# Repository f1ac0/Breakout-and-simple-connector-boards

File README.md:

# Breakout and simple connector boards
This repository contains mostly simple KiCAD PCBs boards that I needed at some point.

# Disclaimer
This is a hobbyist project, it comes with no warranty and no support.

I publish my work under the CC-BY-NC-SA license.

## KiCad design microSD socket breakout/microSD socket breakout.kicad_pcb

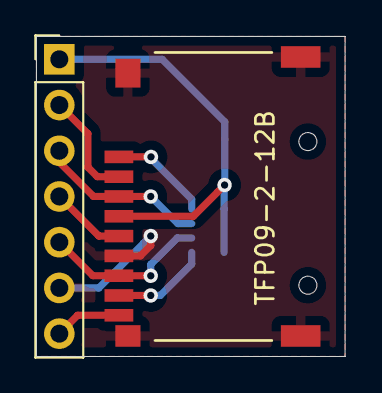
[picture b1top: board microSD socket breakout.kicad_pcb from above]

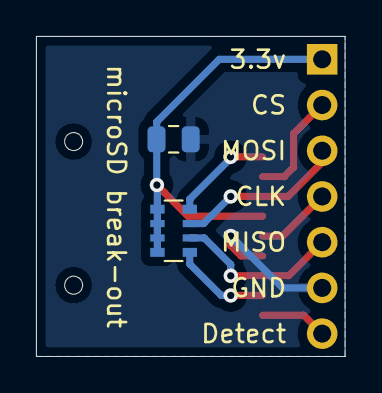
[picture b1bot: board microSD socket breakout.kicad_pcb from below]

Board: 2 copper layers, 17.1 x 17.8 mm, 4 parts (2 on the bottom side), 9 nets.

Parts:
C1: C_Small; C_0805_2012Metric
J1: Micro_SD_Card_Det_1Pin; TFP09-2-12B
J2: Conn_01x07; PinHeader_1x07_P2.54mm_Vertical
RN1: R_Pack04; R_Array_Convex_4x0603

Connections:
+3.3V: C1.1, J1.4 (VDD), J2.1, RN1.5 (R4.2), RN1.6 (R3.2), RN1.7 (R2.2), RN1.8 (R1.2)
/SD_DETECT: J1.9 (CARD_DETECTION), J2.7
/SPI_CLK: J1.5 (CLK), J2.4
/SPI_CS: J1.2 (DAT3/CD), J2.2
/SPI_MISO: J1.7 (DAT0), J2.5, RN1.2 (R2.1)
/SPI_MOSI: J1.3 (CMD), J2.3, RN1.3 (R3.1)
GND: C1.2, J1.6 (VSS), J1.10 (SHIELD), J2.6
unnamed: J1.1 (DAT2), RN1.4 (R4.1)
unnamed: J1.8 (DAT1), RN1.1 (R1.1)

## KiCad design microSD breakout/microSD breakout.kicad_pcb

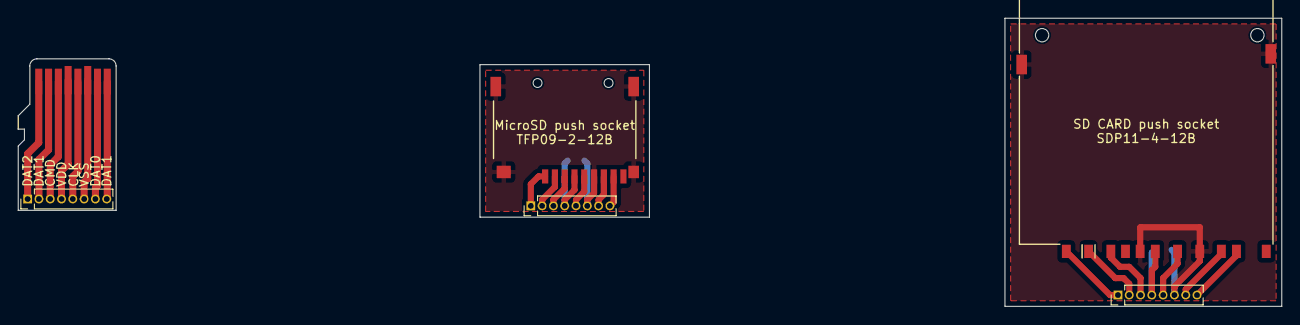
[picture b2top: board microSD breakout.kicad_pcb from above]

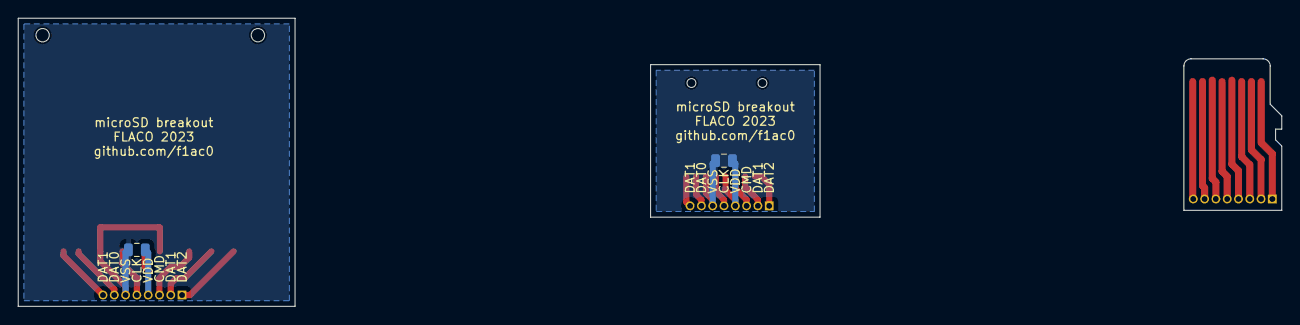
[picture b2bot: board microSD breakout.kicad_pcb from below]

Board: 2 copper layers, 142.0 x 32.4 mm, 8 parts (2 on the bottom side), 24 nets.

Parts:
C1, C2: C_Small; C_0805_2012Metric
J1, J4, J6: Conn_01x08; PinHeader_1x08_P1.27mm_Vertical
J2: Micro_SD_Card_Det_1Pin; TFP09-2-12B
J3: Micro_SD_Card; Micro_SD
J5: SD_Card; Conn_SDcard

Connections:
/SD_CLK: J3.5 (CLK), J4.5
/SD_CMD: J3.3 (CMD), J4.3
/SD_DAT0: J3.7 (DAT0), J4.7
/SD_DAT1: J3.8 (DAT1), J4.8
/SD_DAT2: J3.1 (DAT2), J4.1
/SD_DAT3: J3.2 (DAT3/CD), J4.2
/SD_VDD: J3.4 (VDD), J4.4
/SD_VSS: J3.6 (VSS), J4.6
/SOCKSD_CLK: J5.5 (CLK), J6.5
/SOCKSD_CMD: J5.2 (CMD), J6.3
/SOCKSD_DAT0: J5.7 (DAT0), J6.7
/SOCKSD_DAT1: J5.8 (DAT1), J6.8
/SOCKSD_DAT2: J5.9 (DAT2), J6.1
/SOCKSD_DAT3: J5.1 (CD/DAT3), J6.2
/SOCKSD_VDD: C2.1, J5.4 (VDD), J6.4
/SOCKSD_VSS: C2.2, J5.3 (VSS), J5.6 (VSS), J5.12 (SHELL1), J5.13 (SHELL2), J6.6
/SOCK_CLK: J1.5, J2.5 (CLK)
/SOCK_CMD: J1.3, J2.3 (CMD)
/SOCK_DAT0: J1.7, J2.7 (DAT0)
/SOCK_DAT1: J1.8, J2.8 (DAT1)
/SOCK_DAT2: J1.1, J2.1 (DAT2)
/SOCK_DAT3: J1.2, J2.2 (DAT3/CD)
/SOCK_VDD: C1.1, J1.4, J2.4 (VDD)
/SOCK_VSS: C1.2, J1.6, J2.6 (VSS), J2.10 (SHIELD)

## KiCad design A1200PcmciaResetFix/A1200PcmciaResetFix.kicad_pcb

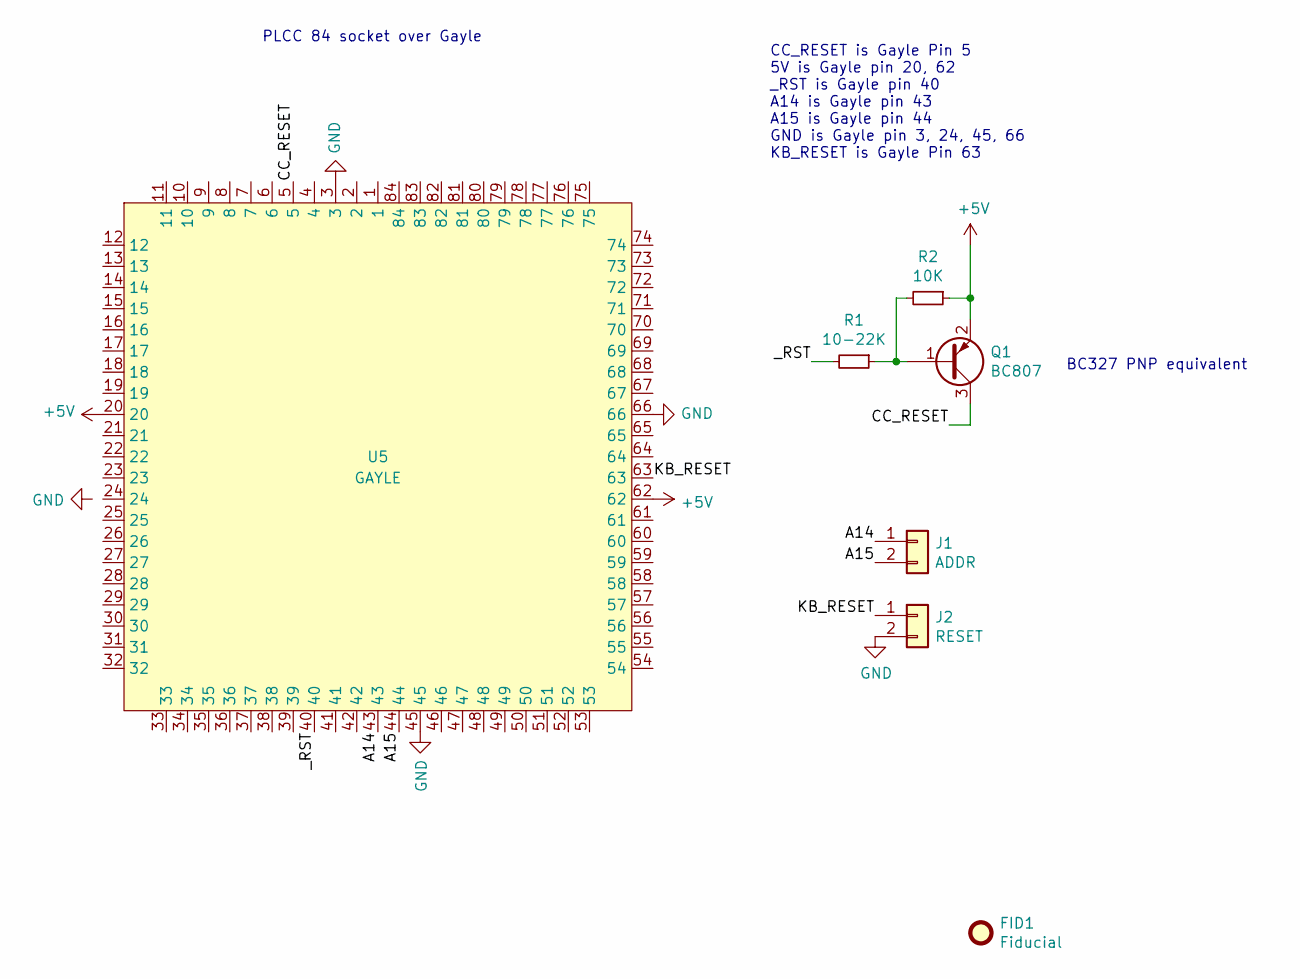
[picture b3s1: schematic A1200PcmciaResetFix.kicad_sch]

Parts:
FID1: Fiducial; CC_BY_NC_SA_square_silkscreen
J1: ADDR; PinHeader_1x02_P2.54mm_Vertical
J2: RESET; PinHeader_1x02_P2.54mm_Vertical
Q1: BC807; SOT-23
R1: 10-22K; R_0805_2012Metric
R2: 10K; R_0805_2012Metric
U5: GAYLE; PLCC-84_THT-SocketOnTop

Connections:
+5V: Q1.2 (E), R2.1, U5.20, U5.62
/A14: J1.1, U5.43
/A15: J1.2, U5.44
/CC_RESET: Q1.3 (C), U5.5
/KB_RESET: J2.1, U5.63
/_RST: R1.2, U5.40
GND: J2.2, U5.3, U5.45, U5.66
unnamed: Q1.1 (B), R1.1, R2.2

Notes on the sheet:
CC_RESET is Gayle Pin 5 5V is Gayle pin 20, 62 _RST is Gayle pin 40 A14 is Gayle pin 43 A15 is Gayle pin 44 GND is Gayle pin 3, 24, 45, 66 KB_RESET is Gayle Pin 63
BC327 PNP equivalent
PLCC 84 socket over Gayle

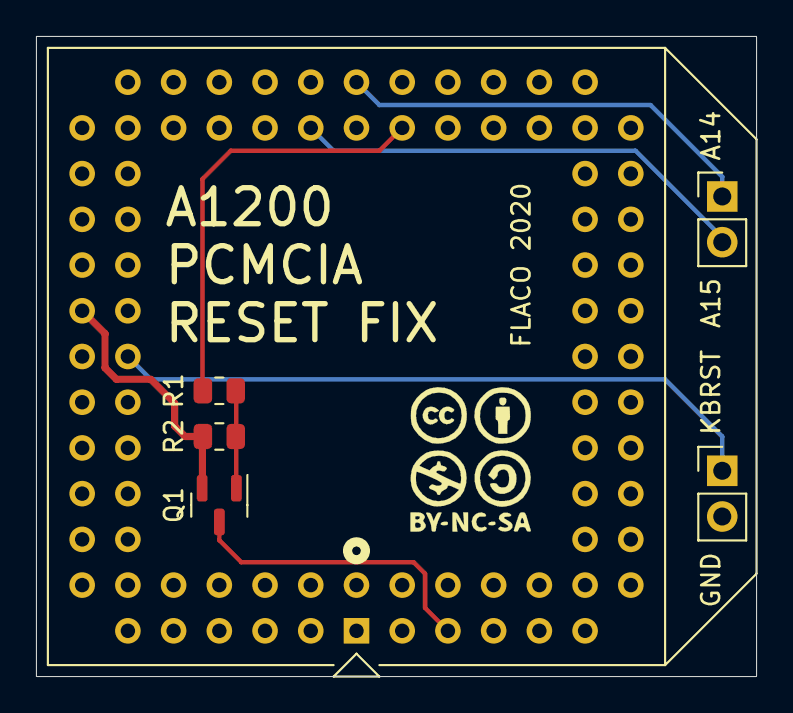
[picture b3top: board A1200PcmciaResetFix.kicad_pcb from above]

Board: 2 copper layers, 40.0 x 35.6 mm, 7 parts (1 on the bottom side), 8 nets.

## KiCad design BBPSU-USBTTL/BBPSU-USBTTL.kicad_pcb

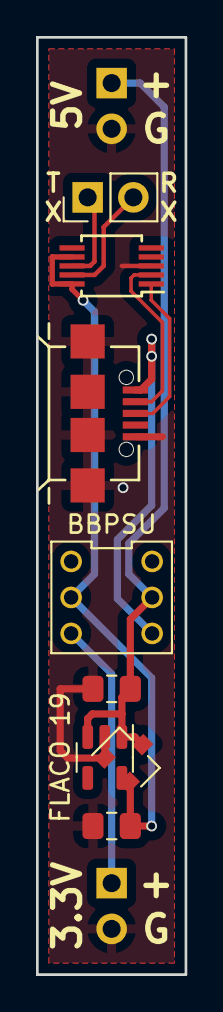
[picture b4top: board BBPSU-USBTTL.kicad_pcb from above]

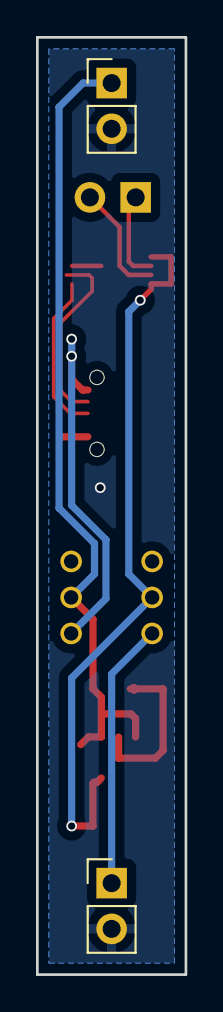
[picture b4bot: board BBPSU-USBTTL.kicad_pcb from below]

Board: 2 copper layers, 8.3 x 52.1 mm, 10 parts (2 on the bottom side), 9 nets.

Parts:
C2, C3: C; C_0805_2012Metric_Pad1.18x1.45mm_HandSolder
J1: USB_OTG; USB-MICRO-B
J3, J4, J5: Conn_01x02; PinHeader_1x02_P2.54mm_Vertical
SW1: SW_DPDT_x2; SW_PUSH_Self-locking_5.8mm
U1: SPX3819M5-L-3-3; SOT-23-5
U2: XC6206PxxxMR; SOT-23
U3: CH340E; MSOP-10_3x3mm_P0.5mm

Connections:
+3.3V: C3.1, SW1.2 (B), U1.5 (OUT), U2.2 (VO), U3.7 (VCC), U3.10 (V3)
+5V: J1.1 (VBUS), SW1.6 (C)
/D+: J1.3 (D+), U3.1 (UD+)
/D-: J1.2 (D-), U3.2 (UD-)
/RXD: J5.2, U3.9 (RXD)
/TXD: J5.1, U3.8 (TXD)
GND: C2.2, C3.2, J1.5 (GND), J1.6 (Shield), J3.2, J4.2, U1.2 (GND), U2.1 (GND), U3.3 (GND)
unnamed: J4.1, SW1.3 (C)
unnamed: C2.1, J3.1, SW1.5 (B), U1.1 (IN), U1.3 (EN), U2.3 (VI)

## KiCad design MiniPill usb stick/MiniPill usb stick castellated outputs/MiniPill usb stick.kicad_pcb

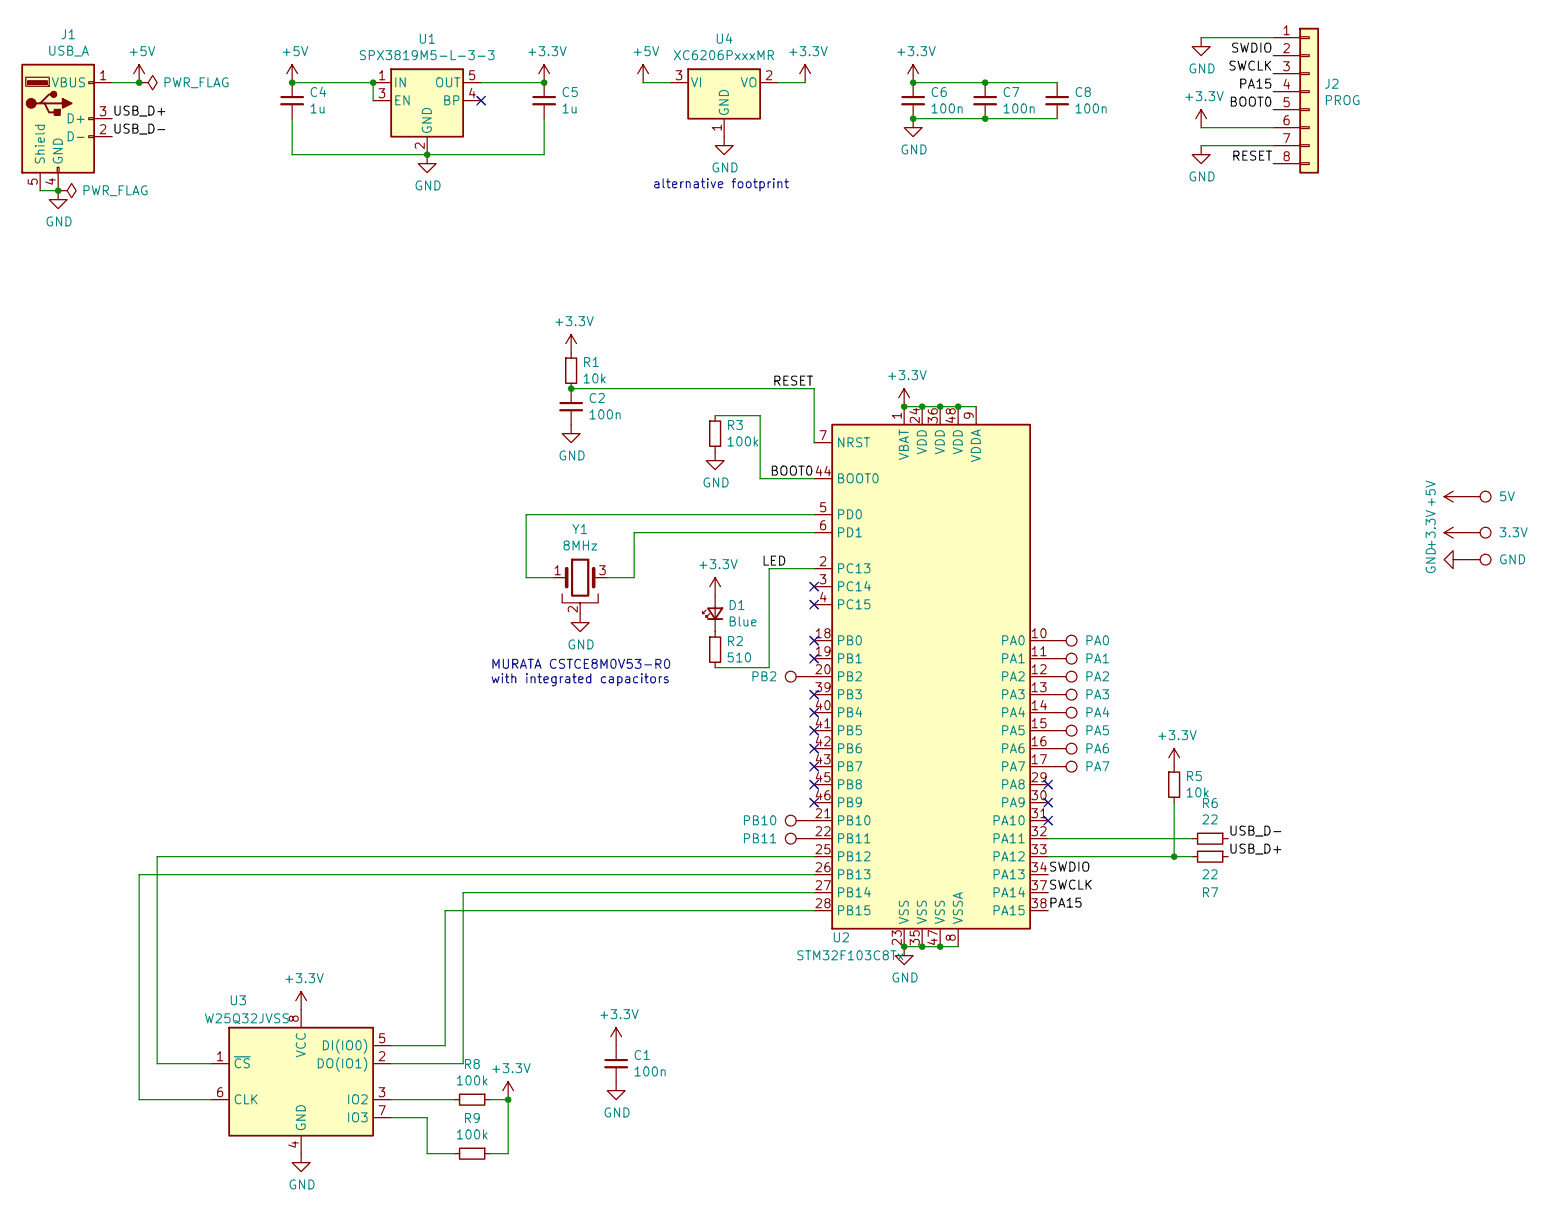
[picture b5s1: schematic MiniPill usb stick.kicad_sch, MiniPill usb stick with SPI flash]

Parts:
C1, C2, C6, C7, C8: 100n; C_0805_2012Metric
C4, C5: 1u; C_0805_2012Metric
D1: Blue; LED_0805_2012Metric
J1: USB_A; USB_A_CNCTech_1001-011-01101_Horizontal
J2: PROG; PinHeader_1x08_P2.54mm_Vertical
R1, R5: 10k; R_0805_2012Metric
R2: 510; R_0805_2012Metric
R3, R8, R9: 100k; R_0805_2012Metric
R6, R7: 22; R_0805_2012Metric
TP_B1: 5V; Pin_THT_Square_Pitch2.54mm
TP_B2: PB2; Pin_THT_Square_Pitch2.54mm
TP_B3: 3.3V; Pin_THT_Square_Pitch2.54mm
TP_B4: GND; Pin_THT_Square_Pitch2.54mm
TP_B5: PA0; Pin_THT_Square_Pitch2.54mm
TP_B6: PA1; Pin_THT_Square_Pitch2.54mm
TP_B7: PA2; Pin_THT_Square_Pitch2.54mm
TP_B8: PA3; Pin_THT_Square_Pitch2.54mm
TP_B9: PA4; Pin_THT_Square_Pitch2.54mm
TP_B10: PB10; Pin_THT_Square_Pitch2.54mm
TP_B11: PB11; Pin_THT_Square_Pitch2.54mm
TP_B12: PA5; Pin_THT_Square_Pitch2.54mm
TP_B13: PA6; Pin_THT_Square_Pitch2.54mm
TP_B14: PA7; Pin_THT_Square_Pitch2.54mm
U1: SPX3819M5-L-3-3; SOT-23-5
U2: STM32F103C8Tx; LQFP-48_7x7mm_P0.5mm
U3: W25Q32JVSS; SOIC-8_5.23x5.23mm_P1.27mm
U4: XC6206PxxxMR; SOT-23
Y1: 8MHz; Resonator_SMD_Murata_CSTxExxV-3Pin_3.0x1.1mm

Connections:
+3.3V: C1.1, C5.1, C6.1, C7.1, C8.1, D1.2 (A), J2.6, R1.1, R5.1, R8.1, R9.1, TP_B3.1, U1.5 (OUT), U2.1 (VBAT), U2.9 (VDDA), U2.24 (VDD), U2.36 (VDD), U2.48 (VDD), U3.8 (VCC), U4.2 (VO)
+5V: C4.1, J1.1 (VBUS), TP_B1.1, U1.1 (IN), U1.3 (EN), U4.3 (VI)
/BOOT0: J2.5, R3.1, U2.44 (BOOT0)
/LED: R2.2, U2.2 (PC13)
/PA15: J2.4, U2.38 (PA15)
/RESET: C2.1, J2.8, R1.2, U2.7 (NRST)
/SWCLK: J2.3, U2.37 (PA14)
/SWDIO: J2.2, U2.34 (PA13)
/USB_D+: J1.3 (D+), R7.1
/USB_D-: J1.2 (D-), R6.1
GND: C1.2, C2.2, C4.2, C5.2, C6.2, C7.2, C8.2, J1.4 (GND), J1.5 (Shield), J2.1, J2.7, R3.2, TP_B4.1, U1.2 (GND), U2.8 (VSSA), U2.23 (VSS), U2.35 (VSS), U2.47 (VSS), U3.4 (GND), U4.1 (GND), Y1.2
unnamed: D1.1 (K), R2.1
unnamed: R5.2, R7.2, U2.33 (PA12)
unnamed: R6.2, U2.32 (PA11)
unnamed: R8.2, U3.3 (IO2)
unnamed: R9.2, U3.7 (IO3)
unnamed: TP_B2.1, U2.20 (PB2)
unnamed: TP_B5.1, U2.10 (PA0)
unnamed: TP_B6.1, U2.11 (PA1)
unnamed: TP_B7.1, U2.12 (PA2)
unnamed: TP_B8.1, U2.13 (PA3)
unnamed: TP_B9.1, U2.14 (PA4)
unnamed: TP_B10.1, U2.21 (PB10)
unnamed: TP_B11.1, U2.22 (PB11)
unnamed: TP_B12.1, U2.15 (PA5)
unnamed: TP_B13.1, U2.16 (PA6)
unnamed: TP_B14.1, U2.17 (PA7)
unnamed: U2.5 (PD0), Y1.1
unnamed: U2.6 (PD1), Y1.3
unnamed: U2.25 (PB12), U3.1 (~CS)
unnamed: U2.26 (PB13), U3.6 (CLK)
unnamed: U2.27 (PB14), U3.2 (DO(IO1))
unnamed: U2.28 (PB15), U3.5 (DI(IO0))

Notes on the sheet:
alternative footprint
MURATA CSTCE8M0V53-R0 with integrated capacitors

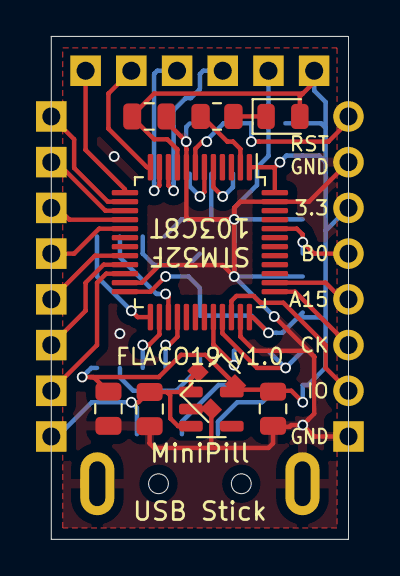
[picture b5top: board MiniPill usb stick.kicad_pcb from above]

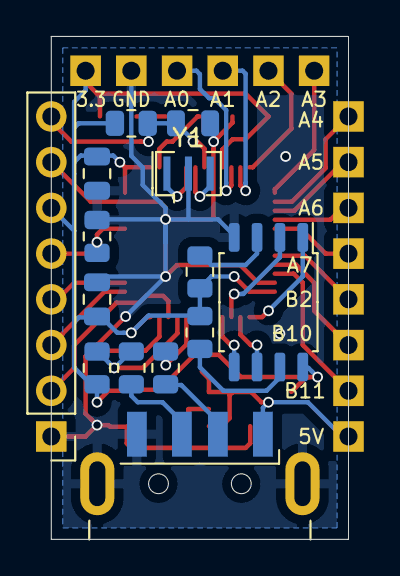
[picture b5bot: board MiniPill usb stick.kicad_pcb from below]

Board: 2 copper layers, 16.5 x 27.9 mm, 37 parts (14 on the bottom side), 33 nets.

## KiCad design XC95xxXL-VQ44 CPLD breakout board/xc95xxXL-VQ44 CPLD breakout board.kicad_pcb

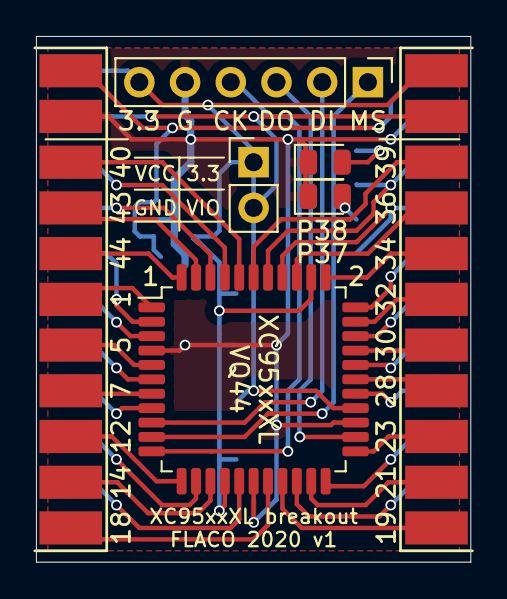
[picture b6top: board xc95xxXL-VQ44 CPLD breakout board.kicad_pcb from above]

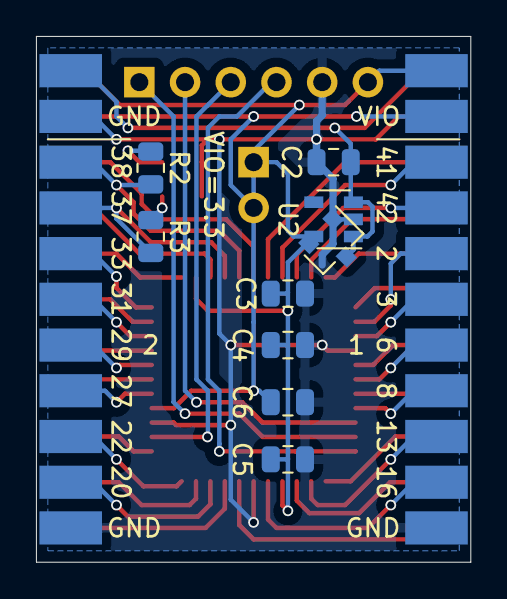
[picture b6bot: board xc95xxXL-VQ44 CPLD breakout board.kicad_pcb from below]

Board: 2 copper layers, 24.1 x 29.2 mm, 16 parts (9 on the bottom side), 43 nets.

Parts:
C2, C3: 1u; C_0805_2012Metric
C4, C5, C6: 100n; C_0805_2012Metric
D1: 4_15; LED_0805_2012Metric
D2: 4_10; LED_0805_2012Metric
J1: JTAG; PinHeader_1x06_P2.54mm_Vertical
J2: Block 1; Pin_Header_2x11_Male_EdgeMount_Pitch2.54mm
J3: Block 2; Pin_Header_2x11_Male_EdgeMount_Pitch2.54mm
JP2: VCCIO; PinHeader_1x02_P2.54mm_Vertical
R2, R3: 2k; R_0805_2012Metric
U1: XC9536XL-VQ44; LQFP-44_10x10mm_P0.8mm
U2: SPX3819M5-L-3-3; SOT-23-5
U3: XC6206PxxxMR; SOT-23

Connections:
+3.3V: C3.1, C4.1, C5.1, C6.1, J1.6, J2.1, J2.3, J3.20, J3.22, JP2.1 (A), JP2.2 (B), U1.15 (VCC), U1.26 (VCCIO), U1.35 (VCC), U2.5 (OUT), U3.2 (VO)
+5V: C2.1, J2.2, J3.21, U2.1 (IN), U2.3 (EN), U3.3 (VI)
/1_1: J2.6, U1.40 (1_1)
/1_2: J2.5, U1.41 (1_2)
/1_3: J2.8, U1.43 (1_3/GCK1)
/1_4: J2.7, U1.42 (1_4)
/1_5: J2.10, U1.44 (1_5/GCK2)
/1_6: J2.9, U1.2 (1_6)
/1_7: J2.12, U1.1 (1_7/GCK3)
/1_8: J2.11, U1.3 (1_8)
/1_9: J2.14, U1.5 (1_9)
/1_10: J2.13, U1.6 (1_10)
/1_11: J2.16, U1.7 (1_11)
/1_12: J2.15, U1.8 (1_12)
/1_13: J2.18, U1.12 (1_13)
/1_14: J2.17, U1.13 (1_14)
/1_15: J2.20, U1.14 (1_15)
/1_16: J2.19, U1.16 (1_16)
/1_17: J2.22, U1.18 (1_17)
/2_1: J3.18, U1.39 (2_1)
/2_2: J3.17, R2.1, U1.38 (2_2)
/2_3: J3.16, U1.36 (2_3/GTS1)
/2_4: J3.15, R3.1, U1.37 (2_4)
/2_5: J3.14, U1.34 (2_5/GTS2)
/2_6: J3.13, U1.33 (2_6/GSR)
/2_7: J3.12, U1.32 (2_7)
/2_8: J3.11, U1.31 (2_8)
/2_9: J3.10, U1.30 (2_9)
/2_10: J3.9, U1.29 (2_10)
/2_11: J3.8, U1.28 (2_11)
/2_12: J3.7, U1.27 (2_12)
/2_13: J3.6, U1.23 (2_13)
/2_14: J3.5, U1.22 (2_14)
/2_15: J3.4, U1.21 (2_15)
/2_16: J3.3, U1.20 (2_16)
/2_17: J3.2, U1.19 (2_17)
/TCK: J1.4, U1.11 (TCK)
/TDI: J1.2, U1.9 (TDI)
/TDO: J1.3, U1.24 (TDO)
/TMS: J1.1, U1.10 (TMS)
GND: C2.2, C3.2, C4.2, C5.2, C6.2, D1.1 (K), D2.1 (K), J1.5, J2.4, J2.21, J3.1, J3.19, U1.4 (GND), U1.17 (GND), U1.25 (GND), U2.2 (GND), U3.1 (GND)
unnamed: D1.2 (A), R2.2
unnamed: D2.2 (A), R3.2

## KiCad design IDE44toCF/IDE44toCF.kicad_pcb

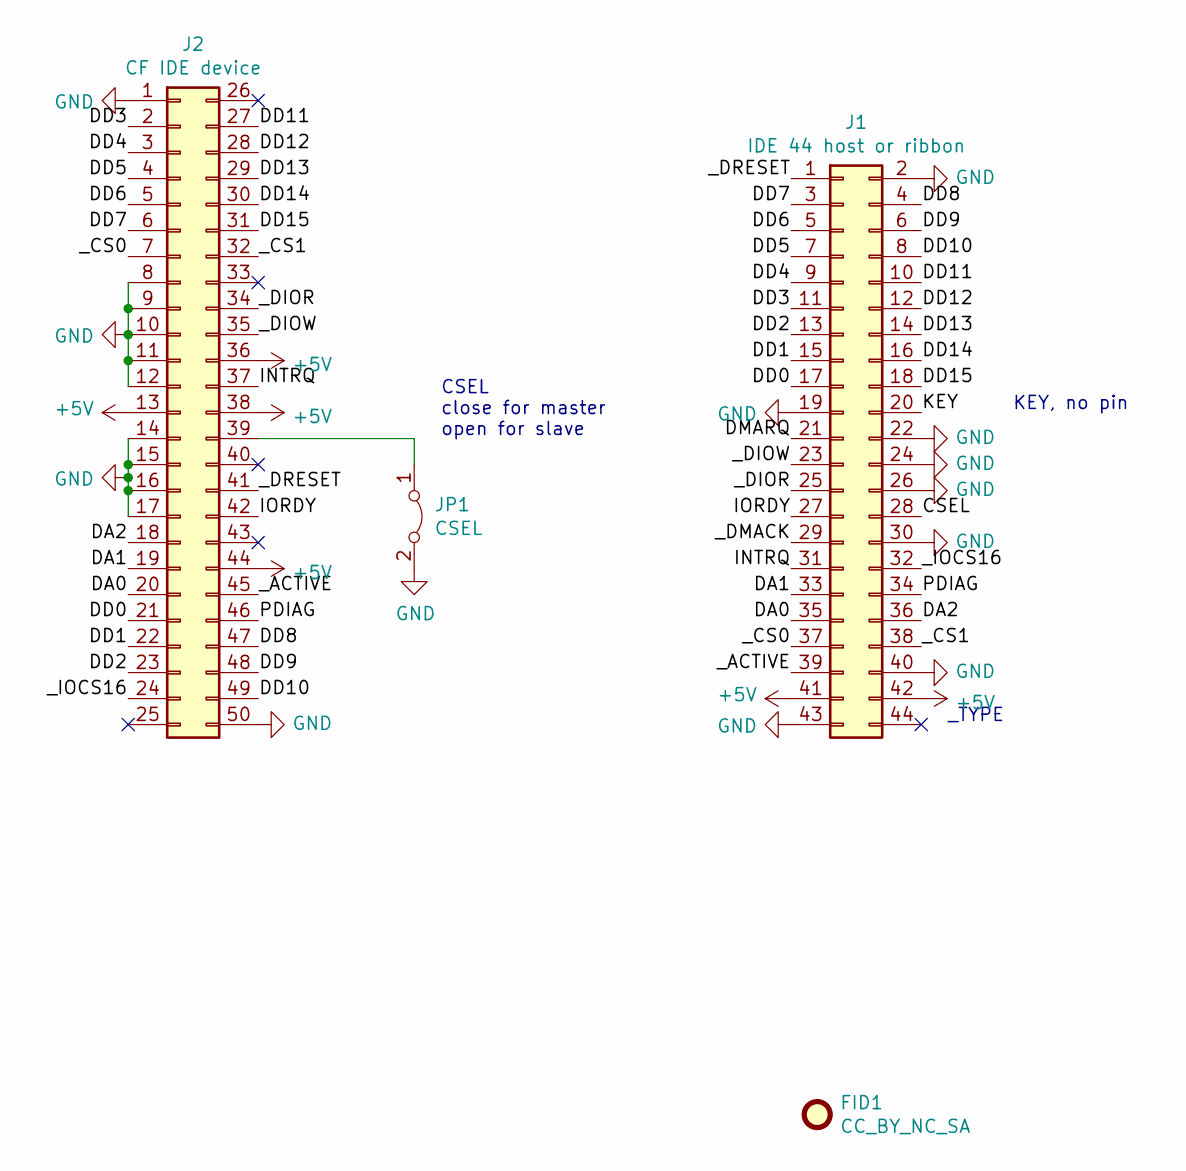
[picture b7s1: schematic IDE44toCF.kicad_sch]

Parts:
FID1: CC_BY_NC_SA; CC_BY_NC_SA_long_silkscreen
J1: IDE 44 host or ribbon; PinHeader_2x22_P2.00mm_Vertical
J2: CF IDE device; CF_male_edge_connector
JP1: CSEL; SolderJumper-2_P1.3mm_Open_RoundedPad1.0x1.5mm

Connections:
+5V: J1.41, J1.42, J2.13, J2.36, J2.38, J2.44
/CSEL: J1.28
/DA0: J1.35, J2.20
/DA1: J1.33, J2.19
/DA2: J1.36, J2.18
/DD0: J1.17, J2.21
/DD1: J1.15, J2.22
/DD2: J1.13, J2.23
/DD3: J1.11, J2.2
/DD4: J1.9, J2.3
/DD5: J1.7, J2.4
/DD6: J1.5, J2.5
/DD7: J1.3, J2.6
/DD8: J1.4, J2.47
/DD9: J1.6, J2.48
/DD10: J1.8, J2.49
/DD11: J1.10, J2.27
/DD12: J1.12, J2.28
/DD13: J1.14, J2.29
/DD14: J1.16, J2.30
/DD15: J1.18, J2.31
/DMARQ: J1.21
/INTRQ: J1.31, J2.37
/IORDY: J1.27, J2.42
/KEY: J1.20
/PDIAG: J1.34, J2.46
/_ACTIVE: J1.39, J2.45
/_CS0: J1.37, J2.7
/_CS1: J1.38, J2.32
/_DIOR: J1.25, J2.34
/_DIOW: J1.23, J2.35
/_DMACK: J1.29
/_DRESET: J1.1, J2.41
/_IOCS16: J1.32, J2.24
GND: J1.2, J1.19, J1.22, J1.24, J1.26, J1.30, J1.40, J1.43, J2.1, J2.8, J2.9, J2.10, J2.11, J2.12, J2.14, J2.15, J2.16, J2.17, J2.50, JP1.2 (B)
unnamed: J2.39, JP1.1 (A)

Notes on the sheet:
CSEL close for master open for slave
KEY, no pin
_TYPE

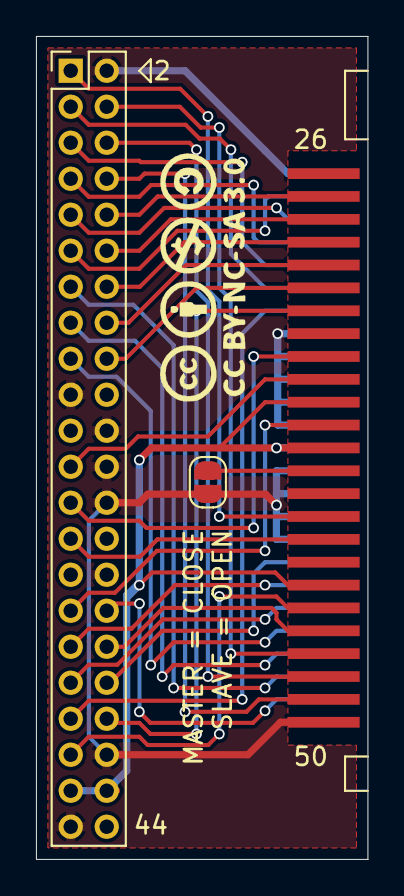
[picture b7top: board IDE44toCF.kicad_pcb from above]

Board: 2 copper layers, 18.4 x 45.7 mm, 4 parts (0 on the bottom side), 32 nets.

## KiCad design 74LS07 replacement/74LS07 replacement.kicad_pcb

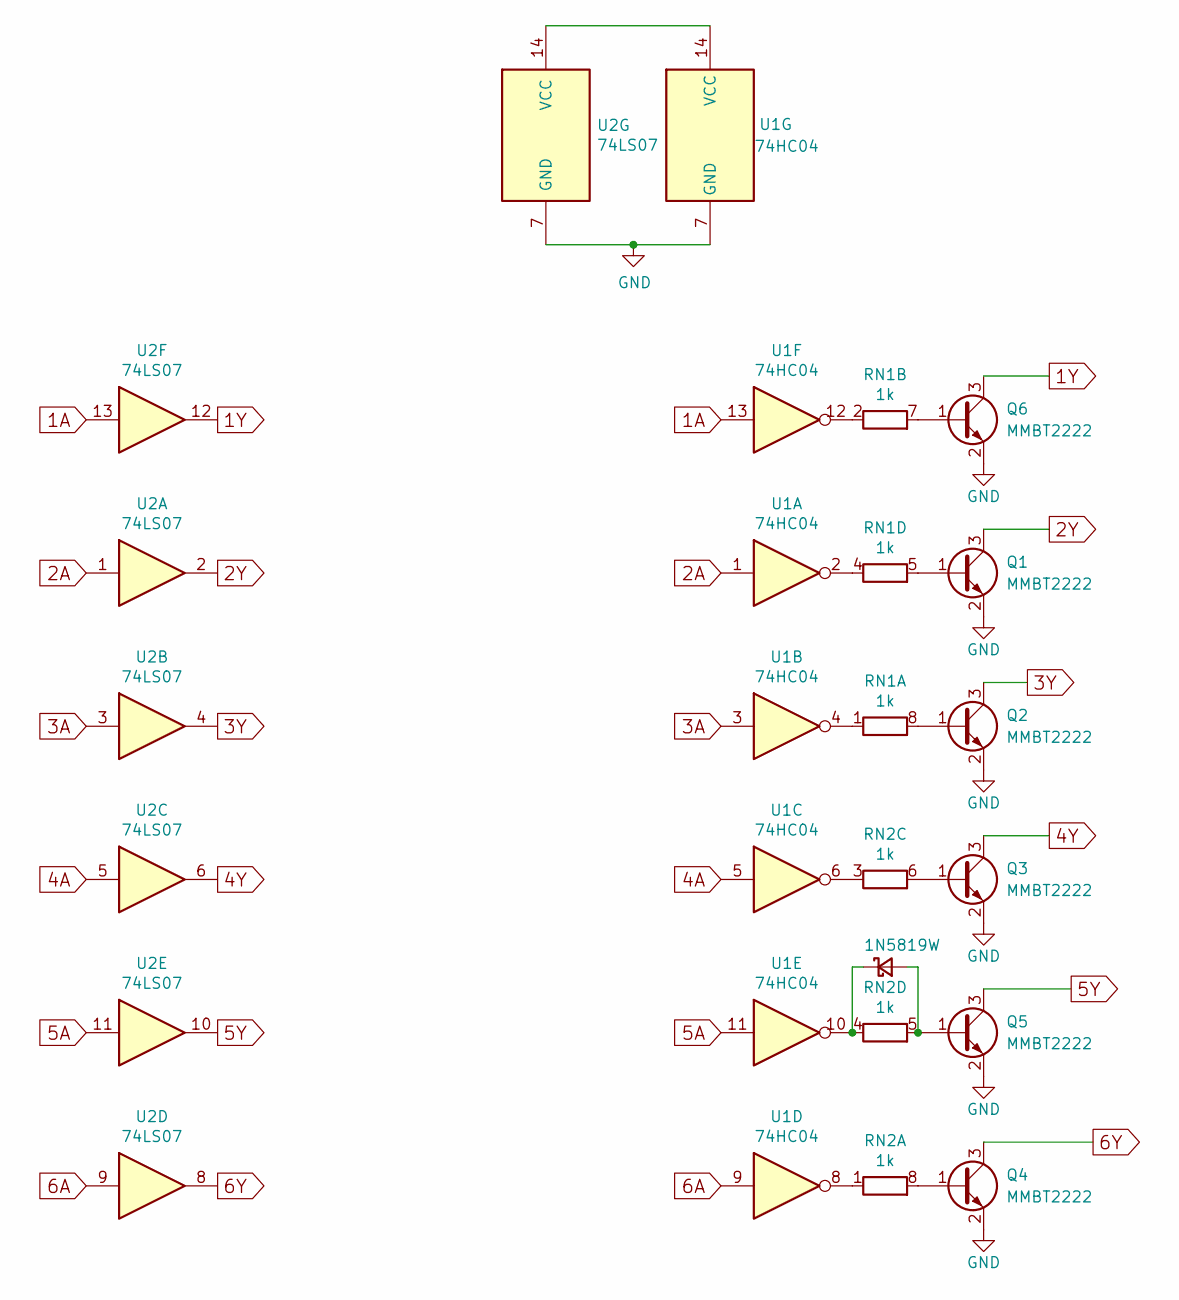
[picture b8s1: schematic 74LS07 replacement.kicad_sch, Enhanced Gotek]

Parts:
Q1, Q2, Q3, Q4, Q5, Q6: MMBT2222; SOT-23
RN1, RN2: 1k; R_Array_Convex_4x0603
U1: 74HC04; SOIC-14_3.9x8.7mm_P1.27mm
U2: 74LS07; SOIC-14_3.9x8.7mm_P1.27mm_replacement

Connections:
1A: U1.13, U2.13
1Y: Q6.3 (C), U2.12
2A: U1.1, U2.1
2Y: Q1.3 (C), U2.2
3A: U1.3, U2.3
3Y: Q2.3 (C), U2.4
4A: U1.5, U2.5
4Y: Q3.3 (C), U2.6
5A: U1.11, U2.11
5Y: Q5.3 (C), U2.10
6A: U1.9, U2.9
6Y: Q4.3 (C), U2.8
GND: Q1.2 (E), Q2.2 (E), Q3.2 (E), Q4.2 (E), Q5.2 (E), Q6.2 (E), U1.7 (GND), U2.7 (GND)
unnamed 13: RN2.4 (R4.1), U1.10; also elsewhere on the board
unnamed 14: Q5.1 (B), RN2.5 (R4.2); also elsewhere on the board
unnamed: Q1.1 (B), RN1.5 (R4.2)
unnamed: Q2.1 (B), RN1.8 (R1.2)
unnamed: Q3.1 (B), RN2.6 (R3.2)
unnamed: Q4.1 (B), RN2.8 (R1.2)
unnamed: Q6.1 (B), RN1.7 (R2.2)
unnamed: RN1.1 (R1.1), U1.4
unnamed: RN1.2 (R2.1), U1.12
unnamed: RN1.4 (R4.1), U1.2
unnamed: RN2.1 (R1.1), U1.8
unnamed: RN2.3 (R3.1), U1.6
unnamed: U1.14 (VCC), U2.14 (VCC)

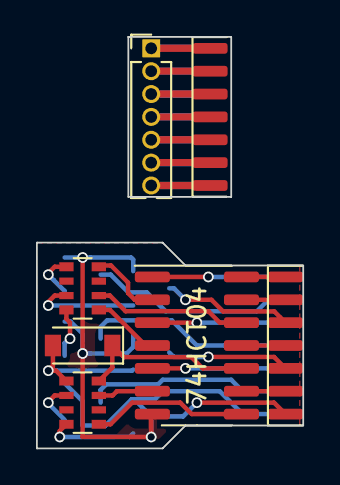
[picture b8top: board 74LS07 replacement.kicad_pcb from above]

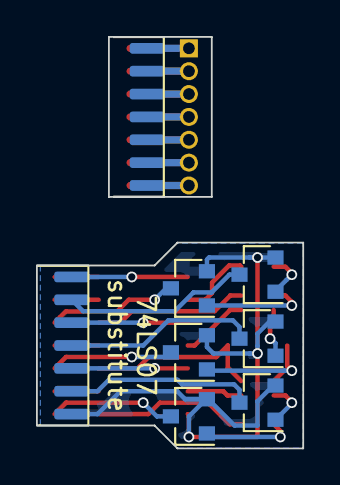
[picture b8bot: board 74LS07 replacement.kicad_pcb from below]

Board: 2 copper layers, 14.8 x 22.9 mm, 11 parts (6 on the bottom side), 26 nets.

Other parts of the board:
DID1: 1N5819W; D_SOD-123

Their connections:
unnamed 13: DID1.1 (K); also elsewhere on the board
unnamed 14: DID1.2 (A); also elsewhere on the board

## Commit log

2022-10-07 Respository init with KiCAD files, Readme and License. All the KiCAD files are converted to KiCAD 6.
2022-10-08 Addition of 'A600-1200KeyboardSocket' and 'A1200PcmciaResetFix'
2022-10-22 A600-1200KeyboardSocket : better symbol for PLCC socket
2022-11-03 Addition of 'BBPSU-USBTTL'
2022-11-23 A1200PcmciaResetFix, A600-1200KeyboardSocket : update socket symbol and footprint, no PCB change
2023-05-26 Addition of 'microSD breakout' which is in fact an extension cable adapter that may work with my PiStorm'X boards. Renamed the microSD SPI socket breakout as 'microSD socket breakout'.

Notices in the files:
A1200PcmciaResetFix/A1200PcmciaResetFix.kicad_pcb:
FLACO 2020, licence of this PCB is CC-BY-NC-SA
A1200PcmciaResetFix/A1200PcmciaResetFix.kicad_sch:
FLACO 2020, licence of this schematic is CC-BY-NC-SA
BBPSU-USBTTL/BBPSU-USBTTL.kicad_pcb:
FLACO 2022, licence of this PCB is CC-BY-NC-SA
MiniPill usb stick/MiniPill usb stick castellated outputs/MiniPill usb stick.kicad_pcb:
FLACO 2019, licence of this PCB is CC-BY-NC-SA
MiniPill usb stick/MiniPill usb stick castellated outputs/MiniPill usb stick.kicad_sch:
FLACO 2019, licence of this schematic is CC-BY-NC-SA
